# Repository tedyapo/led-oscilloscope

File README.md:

# led-oscilloscope
Simple (toy-like) LED oscilloscope

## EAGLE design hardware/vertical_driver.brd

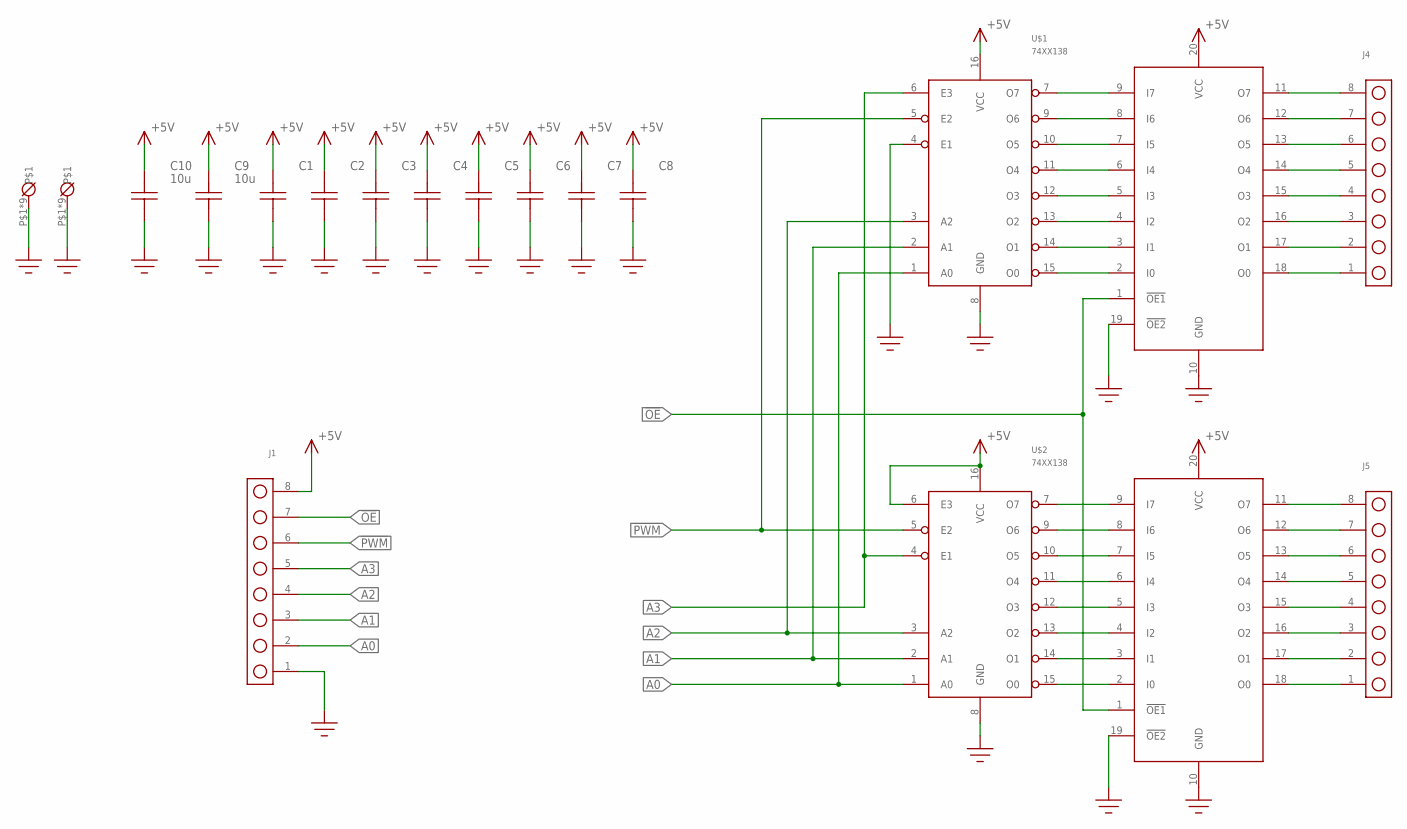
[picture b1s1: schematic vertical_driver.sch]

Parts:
C1, C2, C3, C4, C5, C6, C7, C8: C0805; 0805
C9, C10: 10u; 1206
J1, J4, J5: HEADER_8P
U$1, U$2: 74XX138; SOIC-16
U$8, U$9: 74XX540; SOIC-20W
U$34, U$35: MOUNTING_HOLE; MOUNTING_HOLE_#4

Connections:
!OE!: J1.7, U$8.1 (!OE1!), U$9.1 (!OE1!)
!PWM!: J1.6, U$1.5 (E2), U$2.5 (E2)
+5V: C1.P$2, C2.P$2, C3.P$2, C4.P$2, C5.P$2, C6.P$2, C7.P$2, C8.P$2, C9.P$2, C10.P$2, J1.8, U$1.16 (VCC), U$2.6 (E3), U$2.16 (VCC), U$8.20 (VCC), U$9.20 (VCC)
A0: J1.2, U$1.1 (A0), U$2.1 (A0)
A1: J1.3, U$1.2 (A1), U$2.2 (A1)
A2: J1.4, U$1.3 (A2), U$2.3 (A2)
A3: J1.5, U$1.6 (E3), U$2.4 (E1)
GND: C1.P$1, C2.P$1, C3.P$1, C4.P$1, C5.P$1, C6.P$1, C7.P$1, C8.P$1, C9.P$1, C10.P$1, J1.1, U$1.4 (E1), U$1.8 (GND), U$2.8 (GND), U$8.10 (GND), U$8.19 (!OE2!), U$9.10 (GND), U$9.19 (!OE2!), U$34.P$1, U$34.P$2, U$34.P$3, U$34.P$4, U$34.P$5, U$34.P$6, U$34.P$7, U$34.P$8, U$34.P$9, U$35.P$1, U$35.P$2, U$35.P$3, U$35.P$4, U$35.P$5, U$35.P$6, U$35.P$7, U$35.P$8, U$35.P$9
unnamed: U$1.7 (O7), U$8.9 (I7)
unnamed: U$1.9 (O6), U$8.8 (I6)
unnamed: U$1.10 (O5), U$8.7 (I5)
unnamed: U$1.11 (O4), U$8.6 (I4)
unnamed: U$1.12 (O3), U$8.5 (I3)
unnamed: U$1.13 (O2), U$8.4 (I2)
unnamed: U$1.14 (O1), U$8.3 (I1)
unnamed: U$1.15 (O0), U$8.2 (I0)
unnamed: J4.8, U$8.11 (O7)
unnamed: J4.7, U$8.12 (O6)
unnamed: J4.6, U$8.13 (O5)
unnamed: J4.5, U$8.14 (O4)
unnamed: J4.4, U$8.15 (O3)
unnamed: J4.3, U$8.16 (O2)
unnamed: J4.2, U$8.17 (O1)
unnamed: J4.1, U$8.18 (O0)
unnamed: U$2.7 (O7), U$9.9 (I7)
unnamed: U$2.9 (O6), U$9.8 (I6)
unnamed: U$2.10 (O5), U$9.7 (I5)
unnamed: U$2.11 (O4), U$9.6 (I4)
unnamed: U$2.12 (O3), U$9.5 (I3)
unnamed: U$2.13 (O2), U$9.4 (I2)
unnamed: U$2.14 (O1), U$9.3 (I1)
unnamed: U$2.15 (O0), U$9.2 (I0)
unnamed: J5.8, U$9.11 (O7)
unnamed: J5.7, U$9.12 (O6)
unnamed: J5.6, U$9.13 (O5)
unnamed: J5.5, U$9.14 (O4)
unnamed: J5.4, U$9.15 (O3)
unnamed: J5.3, U$9.16 (O2)
unnamed: J5.2, U$9.17 (O1)
unnamed: J5.1, U$9.18 (O0)

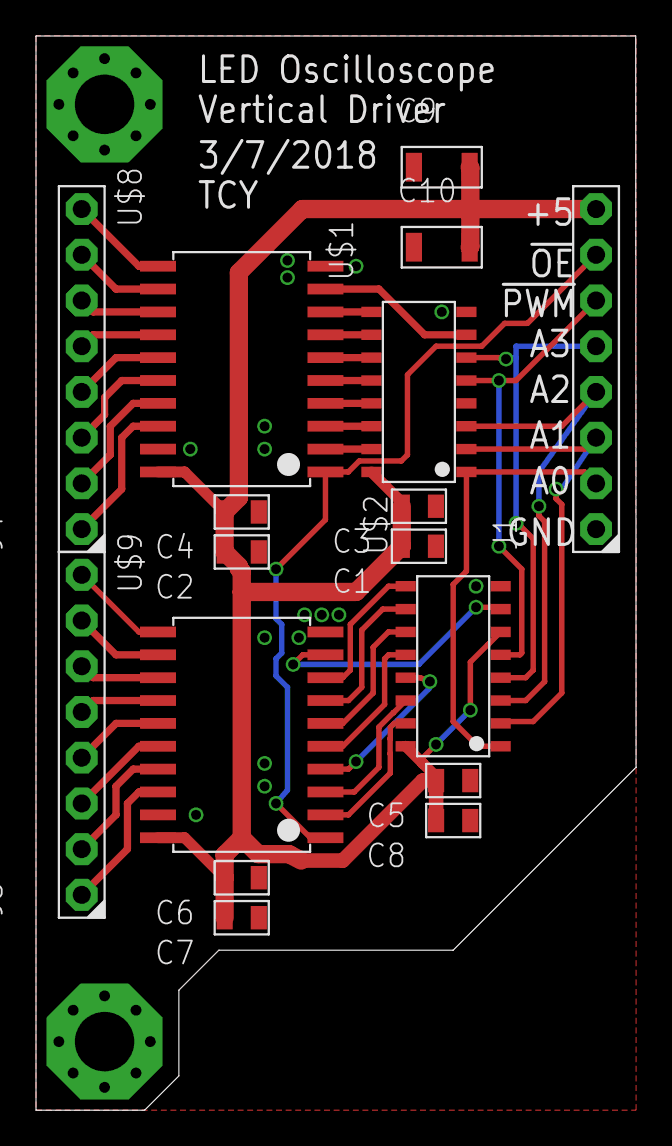
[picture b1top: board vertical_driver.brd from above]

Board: 2 copper layers, 33.3 x 59.7 mm, 19 parts (0 on the bottom side), 40 nets.

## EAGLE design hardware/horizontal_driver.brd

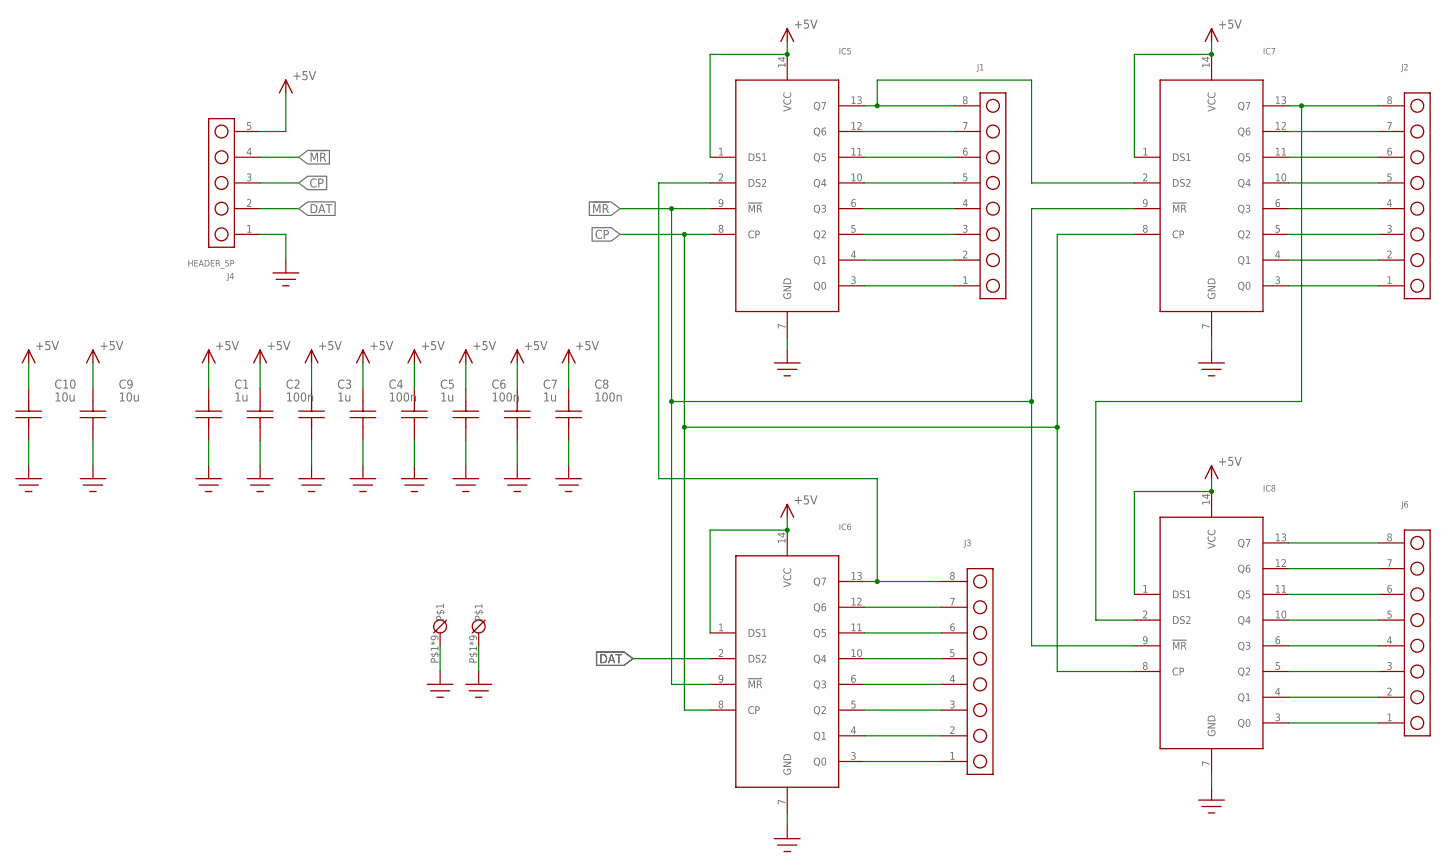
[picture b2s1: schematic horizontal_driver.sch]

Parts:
C1, C3, C5, C7: 1u; 0805
C2, C4, C6, C8: 100n; 0805
C9, C10: 10u; 1206
IC5, IC6, IC7, IC8: 74XX164; SOIC-14
J1, J2, J3, J6: HEADER_8P
J4: HEADER_5P
U$1, U$2: MOUNTING_HOLE; MOUNTING_HOLE_#4

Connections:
!MR!: IC5.9 (!MR!), IC6.9 (!MR!), IC7.9 (!MR!), IC8.9 (!MR!), J4.4
+5V: C1.P$2, C2.P$2, C3.P$2, C4.P$2, C5.P$2, C6.P$2, C7.P$2, C8.P$2, C9.P$2, C10.P$2, IC5.1 (DS1), IC5.14 (VCC), IC6.1 (DS1), IC6.14 (VCC), IC7.1 (DS1), IC7.14 (VCC), IC8.1 (DS1), IC8.14 (VCC), J4.5
C0: IC6.3 (Q0), J3.1
C1: IC6.4 (Q1), J3.2
C2: IC6.5 (Q2), J3.3
C3: IC6.6 (Q3), J3.4
C4: IC6.10 (Q4), J3.5
C5: IC6.11 (Q5), J3.6
C6: IC6.12 (Q6), J3.7
C7: IC5.2 (DS2), IC6.13 (Q7), J3.8
C8: IC5.3 (Q0), J1.1
C9: IC5.4 (Q1), J1.2
C10: IC5.5 (Q2), J1.3
C11: IC5.6 (Q3), J1.4
C12: IC5.10 (Q4), J1.5
C13: IC5.11 (Q5), J1.6
C14: IC5.12 (Q6), J1.7
C15: IC5.13 (Q7), IC7.2 (DS2), J1.8
C16: IC7.3 (Q0), J2.1
C17: IC7.4 (Q1), J2.2
C18: IC7.5 (Q2), J2.3
C19: IC7.6 (Q3), J2.4
C20: IC7.10 (Q4), J2.5
C21: IC7.11 (Q5), J2.6
C22: IC7.12 (Q6), J2.7
C23: IC7.13 (Q7), IC8.2 (DS2), J2.8
C24: IC8.3 (Q0), J6.1
C25: IC8.4 (Q1), J6.2
C26: IC8.5 (Q2), J6.3
C27: IC8.6 (Q3), J6.4
C28: IC8.10 (Q4), J6.5
C29: IC8.11 (Q5), J6.6
C30: IC8.12 (Q6), J6.7
C31: IC8.13 (Q7), J6.8
CP: IC5.8 (CP), IC6.8 (CP), IC7.8 (CP), IC8.8 (CP), J4.3
DAT: IC6.2 (DS2), J4.2
GND: C1.P$1, C2.P$1, C3.P$1, C4.P$1, C5.P$1, C6.P$1, C7.P$1, C8.P$1, C9.P$1, C10.P$1, IC5.7 (GND), IC6.7 (GND), IC7.7 (GND), IC8.7 (GND), J4.1, U$1.P$1, U$1.P$2, U$1.P$3, U$1.P$4, U$1.P$5, U$1.P$6, U$1.P$7, U$1.P$8, U$1.P$9, U$2.P$1, U$2.P$2, U$2.P$3, U$2.P$4, U$2.P$5, U$2.P$6, U$2.P$7, U$2.P$8, U$2.P$9

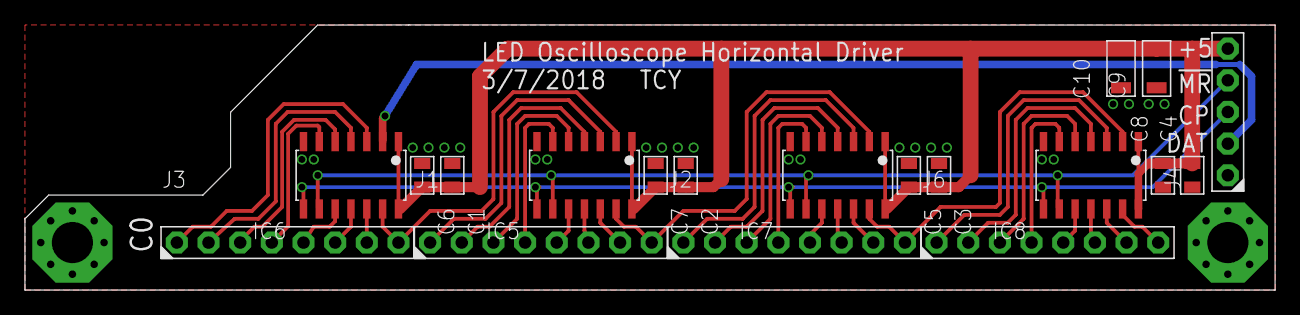
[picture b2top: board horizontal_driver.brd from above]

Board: 2 copper layers, 100.3 x 21.3 mm, 21 parts (0 on the bottom side), 37 nets.

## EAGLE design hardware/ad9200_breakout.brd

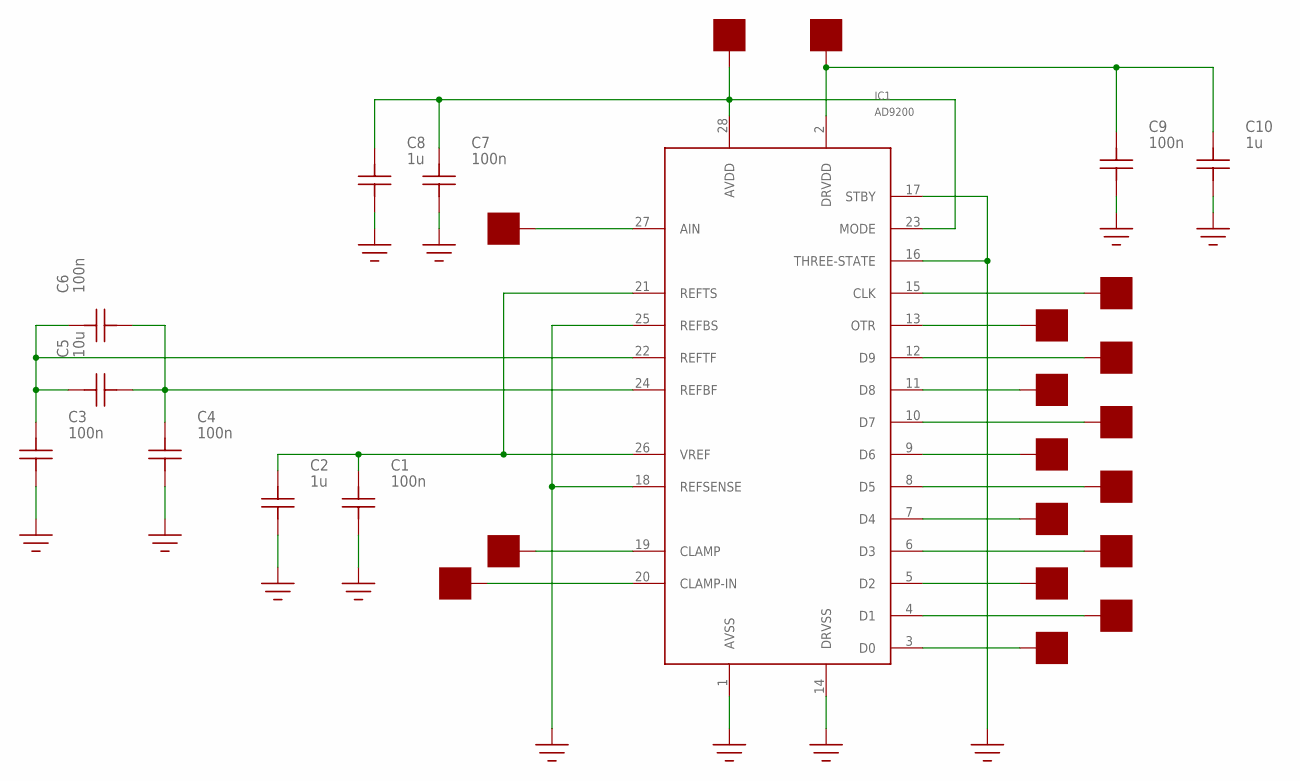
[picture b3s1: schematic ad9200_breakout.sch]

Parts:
C1, C3, C4, C6, C7, C9: 100n; C0603
C2, C8, C10: 1u; C0603
C5: 10u; C0603
IC1: AD9200; SSOP-28
U$5, U$6, U$7, U$8, U$9, U$10, U$11, U$12, U$13, U$14, U$15, U$16, U$17, U$18, U$19, U$20, U$21: PAD50MIL; PAD_50MIL

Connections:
GND: C1.P$1, C2.P$1, C3.P$1, C4.P$1, C7.P$1, C8.P$1, C9.P$1, C10.P$1, IC1.1 (AVSS), IC1.14 (DRVSS), IC1.16 (THREE-STATE), IC1.17 (STBY), IC1.18 (REFSENSE), IC1.25 (REFBS)
unnamed: C4.P$2, C5.P$1, C6.P$1, IC1.24 (REFBF)
unnamed: C1.P$2, C2.P$2, IC1.21 (REFTS), IC1.26 (VREF)
unnamed: C3.P$2, C5.P$2, C6.P$2, IC1.22 (REFTF)
unnamed: C7.P$2, C8.P$2, IC1.23 (MODE), IC1.28 (AVDD), U$18.P$1
unnamed: IC1.3 (D0), U$5.P$1
unnamed: IC1.4 (D1), U$6.P$1
unnamed: IC1.5 (D2), U$7.P$1
unnamed: IC1.6 (D3), U$8.P$1
unnamed: IC1.7 (D4), U$9.P$1
unnamed: IC1.8 (D5), U$10.P$1
unnamed: IC1.9 (D6), U$11.P$1
unnamed: IC1.10 (D7), U$12.P$1
unnamed: IC1.11 (D8), U$13.P$1
unnamed: IC1.12 (D9), U$14.P$1
unnamed: IC1.13 (OTR), U$15.P$1
unnamed: IC1.15 (CLK), U$16.P$1
unnamed: IC1.27 (AIN), U$17.P$1
unnamed: C9.P$2, C10.P$2, IC1.2 (DRVDD), U$19.P$1
unnamed: IC1.19 (CLAMP), U$20.P$1
unnamed: IC1.20 (CLAMP-IN), U$21.P$1

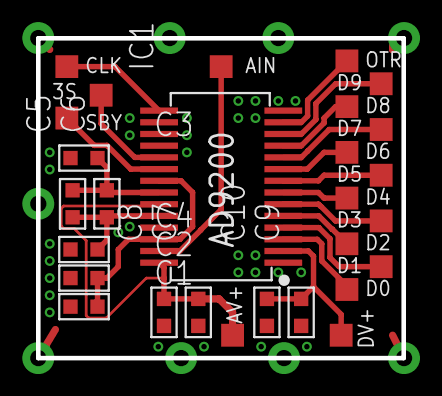
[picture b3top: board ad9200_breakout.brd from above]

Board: 2 copper layers, 20.3 x 17.8 mm, 28 parts (0 on the bottom side), 21 nets.

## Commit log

2018-03-04 first ad9200 breakout order
2018-03-08 horizontal and vertical driver PCBs
